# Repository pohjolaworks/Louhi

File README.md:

## Louhi

Louhi is a DIY 50% mechanical keyboard PCB, with an ortho layout. It is meant to be fairly easy to solder and assemble.

Specs:

    Uses a Pro Micro, Elite-C or Proton-C (or any other controller with same form factor)
    Cherry MX Switches, PCB or plate-mount
    Support for multiple bottom layouts
    Uses one pcb-mount stabilizer
    QMK and Vial Compatible

## Supported layouts
  
## Plate
Gasket-mount universal plate files are located in the FR4-Plate folder. Uses 0.75mm thick gasket material on both sides of the plate.

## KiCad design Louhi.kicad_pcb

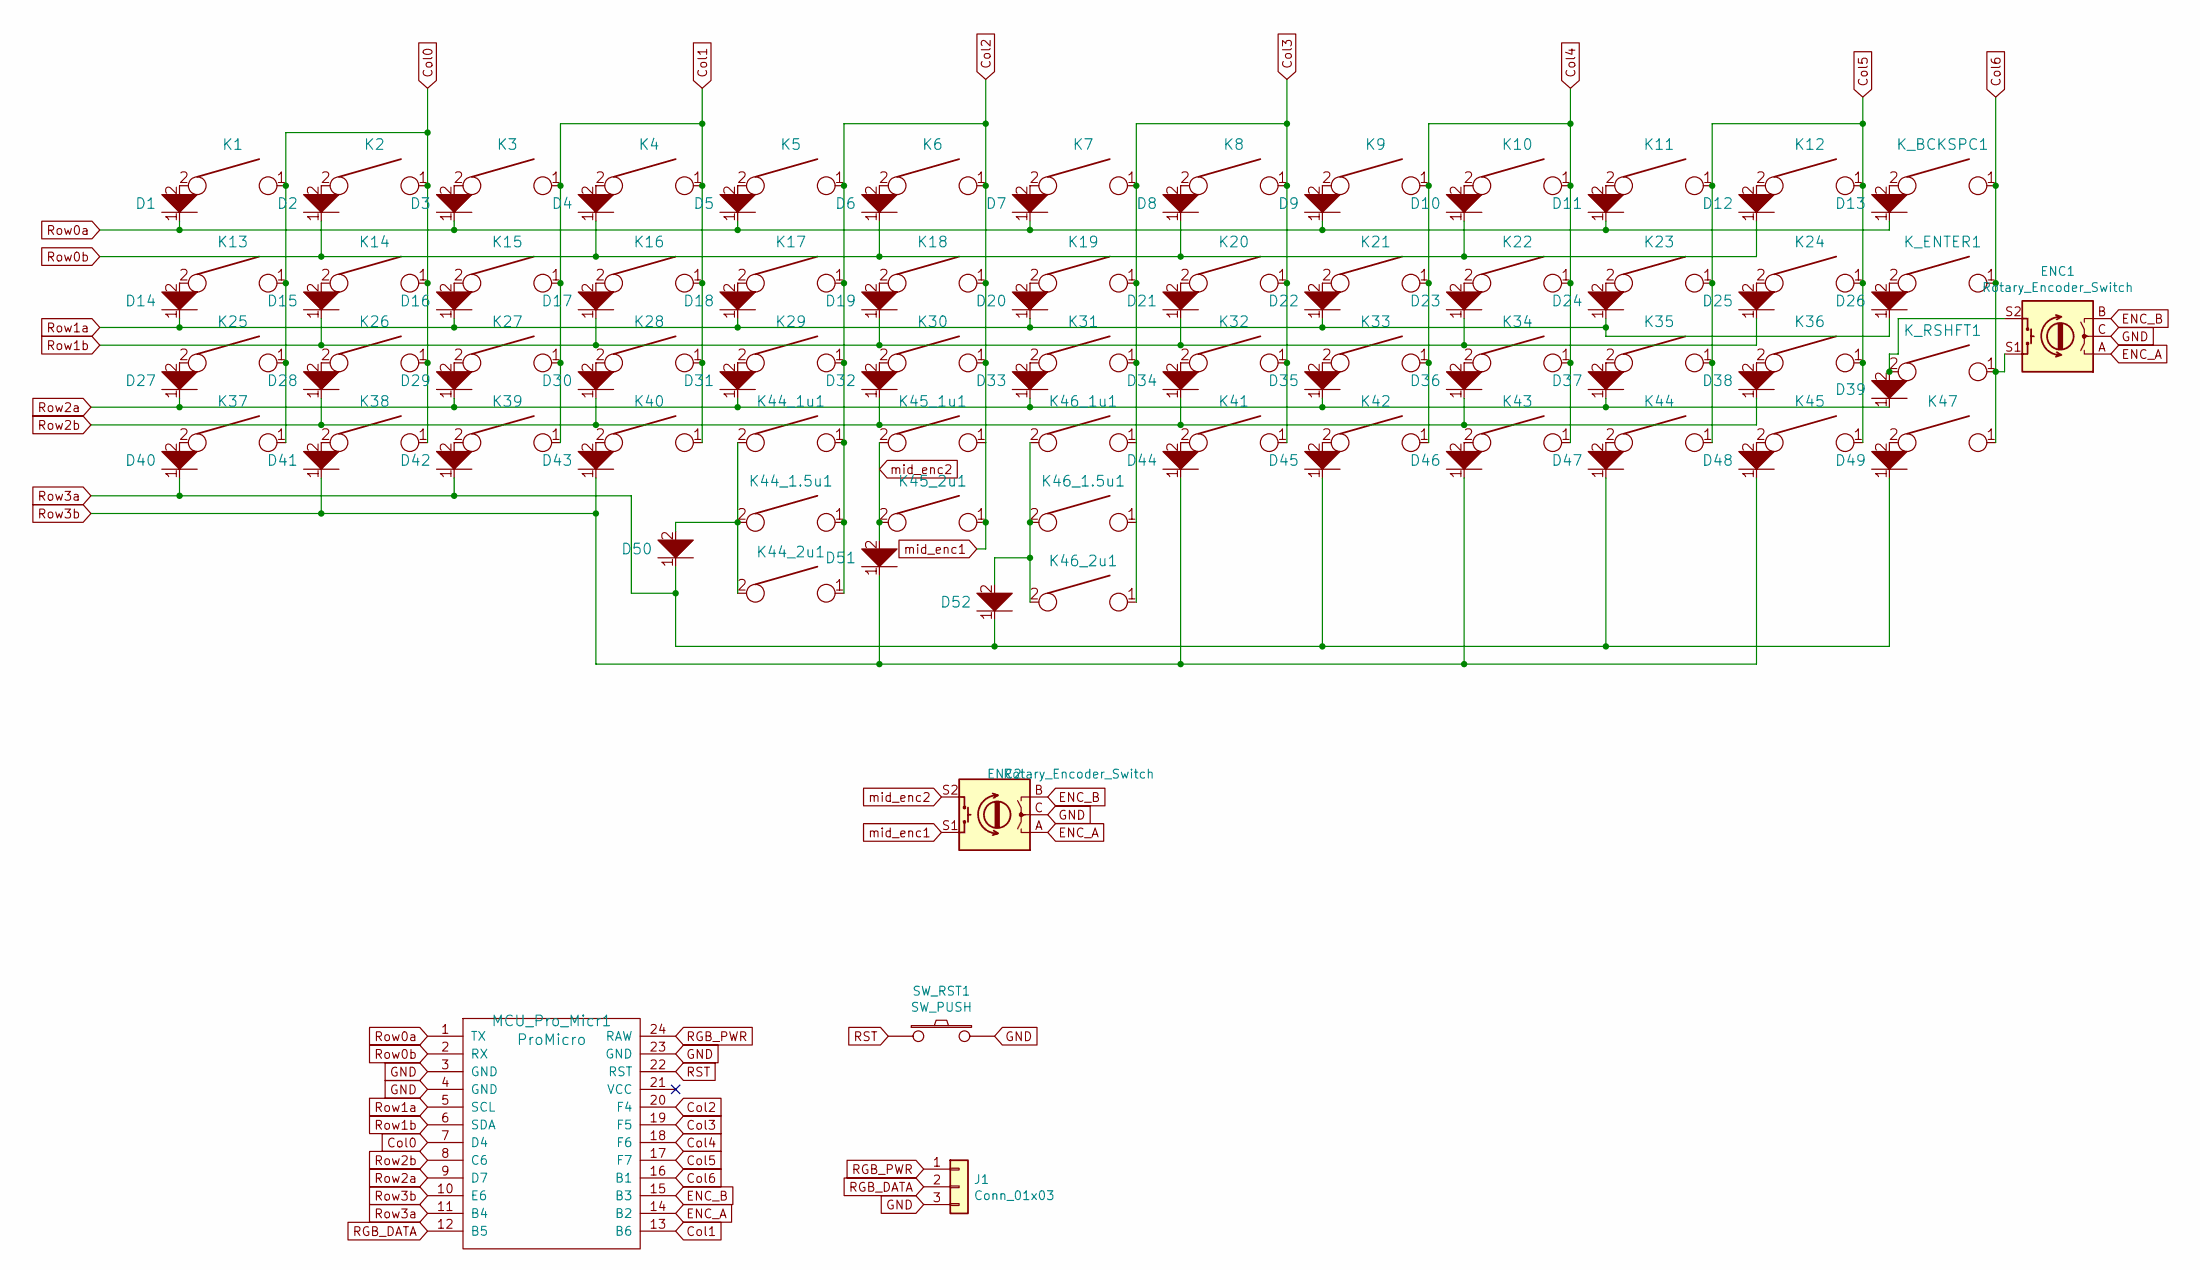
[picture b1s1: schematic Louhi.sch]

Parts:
D1, D2, D3, D4, D5, D6, D7, D8, D9, D10, D11, D12, D13, D14, D15, D16, D17, D18, D19, D20, D21, D22, D23, D24, D25, D26, D27, D28, D29, D30, D31, D32, D33, D34, D35, D36, D37, D38, D39, D40, D41, D42, D43, D44, D45, D46, D47, D48, D49, D50, D51, D52: D; D_SOD123_axial
ENC1, ENC2: Rotary_Encoder_Switch; RotaryEncoder_EC11-no-legs
J1: Conn_01x03; 3_Pin_Jumper
K1, K2, K3, K4, K5, K6, K7, K8, K9, K10, K11, K12, K13, K14, K15, K16, K17, K18, K19, K20, K21, K22, K23, K24, K25, K26, K27, K28, K29, K30, K31, K32, K33, K34, K35, K36, K37, K38, K39, K40, K41, K42, K43, K44, K44_1u1, K45, K45_1u1, K46_1u1, K47: KEYSW; SW_Cherry_MX_1.00u_PCB
K44_1.5u1, K46_1.5u1: KEYSW; SW_Cherry_MX_1.50u_PCB
K44_2u1, K45_2u1, K46_2u1: KEYSW; SW_Cherry_MX_2.00u_PCB
K_BCKSPC1: KEYSW; SW_Cherry_MX_1.00u_PCB
K_ENTER1: KEYSW; SW_Cherry_MX_1.00u_PCB
K_RSHFT1: KEYSW; SW_Cherry_MX_1.00u_PCB
MCU_Pro_Micr1: ProMicro; ArduinoProMicro-BackSide
SW_RST1: SW_PUSH; SW_SPST_TL3342

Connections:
Col0: K1.1, K2.1, K13.1, K14.1, K25.1, K26.1, K37.1, K38.1, MCU_Pro_Micr1.7 (D4)
Col1: K3.1, K4.1, K15.1, K16.1, K27.1, K28.1, K39.1, K40.1, MCU_Pro_Micr1.13 (B6)
Col2: ENC2.S1, K5.1, K6.1, K17.1, K18.1, K29.1, K30.1, K44_1.5u1.1, K44_1u1.1, K44_2u1.1, K45_1u1.1, K45_2u1.1, MCU_Pro_Micr1.20 (F4)
Col3: K7.1, K8.1, K19.1, K20.1, K31.1, K32.1, K41.1, K46_1.5u1.1, K46_1u1.1, K46_2u1.1, MCU_Pro_Micr1.19 (F5)
Col4: K9.1, K10.1, K21.1, K22.1, K33.1, K34.1, K42.1, K43.1, MCU_Pro_Micr1.18 (F6)
Col5: K11.1, K12.1, K23.1, K24.1, K35.1, K36.1, K44.1, K45.1, MCU_Pro_Micr1.17 (F7)
Col6: ENC1.S1, K47.1, K_BCKSPC1.1, K_ENTER1.1, K_RSHFT1.1, MCU_Pro_Micr1.16 (B1)
ENC_A: ENC1.A, ENC2.A, MCU_Pro_Micr1.14 (B2)
ENC_B: ENC1.B, ENC2.B, MCU_Pro_Micr1.15 (B3)
GND: ENC1.C, ENC2.C, J1.3, MCU_Pro_Micr1.3 (GND), MCU_Pro_Micr1.4 (GND), MCU_Pro_Micr1.23 (GND), SW_RST1.2
unnamed: D1.2, K1.2
unnamed: D2.2, K2.2
unnamed: D3.2, K3.2
unnamed: D4.2, K4.2
unnamed: D5.2, K5.2
unnamed: D6.2, K6.2
unnamed: D7.2, K7.2
unnamed: D8.2, K8.2
unnamed: D9.2, K9.2
unnamed: D10.2, K10.2
unnamed: D11.2, K11.2
unnamed: D12.2, K12.2
unnamed: D13.2, K_BCKSPC1.2
unnamed: D14.2, K13.2
unnamed: D15.2, K14.2
unnamed: D16.2, K15.2
unnamed: D17.2, K16.2
unnamed: D18.2, K17.2
unnamed: D19.2, K18.2
unnamed: D20.2, K19.2
unnamed: D21.2, K20.2
unnamed: D22.2, K21.2
unnamed: D23.2, K22.2
unnamed: D24.2, K23.2
unnamed: D25.2, K24.2
unnamed: D26.2, K_ENTER1.2
unnamed: D27.2, K25.2
unnamed: D28.2, K26.2
unnamed: D29.2, K27.2
unnamed: D30.2, K28.2
unnamed: D31.2, K29.2
unnamed: D32.2, K30.2
unnamed: D33.2, K31.2
unnamed: D34.2, K32.2
unnamed: D35.2, K33.2
unnamed: D36.2, K34.2
unnamed: D37.2, K35.2
unnamed: D38.2, K36.2
unnamed: D39.2, ENC1.S2, K_RSHFT1.2
unnamed: D40.2, K37.2
unnamed: D41.2, K38.2
unnamed: D42.2, K39.2
unnamed: D43.2, K40.2
unnamed: D44.2, K41.2
unnamed: D45.2, K42.2
unnamed: D46.2, K43.2
unnamed: D47.2, K44.2
unnamed: D48.2, K45.2
unnamed: D49.2, K47.2
unnamed: D50.2, K44_1.5u1.2, K44_1u1.2, K44_2u1.2
unnamed: D52.2, K46_1.5u1.2, K46_1u1.2, K46_2u1.2
RGB_DATA: J1.2, MCU_Pro_Micr1.12 (B5)
RGB_PWR: J1.1, MCU_Pro_Micr1.24 (RAW)
RST: MCU_Pro_Micr1.22 (RST), SW_RST1.1
Row0a: D1.1, D3.1, D5.1, D7.1, D9.1, D11.1, D13.1, MCU_Pro_Micr1.1 (TX)
Row0b: D2.1, D4.1, D6.1, D8.1, D10.1, D12.1, MCU_Pro_Micr1.2 (RX)
Row1a: D14.1, D16.1, D18.1, D20.1, D22.1, D24.1, D26.1, MCU_Pro_Micr1.5 (SCL)
Row1b: D15.1, D17.1, D19.1, D21.1, D23.1, D25.1, MCU_Pro_Micr1.6 (SDA)
Row2a: D27.1, D29.1, D31.1, D33.1, D35.1, D37.1, D39.1, MCU_Pro_Micr1.9 (D7)
Row2b: D28.1, D30.1, D32.1, D34.1, D36.1, D38.1, MCU_Pro_Micr1.8 (C6)
Row3a: D40.1, D42.1, D45.1, D47.1, D49.1, D50.1, D52.1, MCU_Pro_Micr1.11 (B4)
Row3b: D41.1, D43.1, D44.1, D46.1, D48.1, D51.1, MCU_Pro_Micr1.10 (E6)
mid_enc2: D51.2, ENC2.S2, K45_1u1.2, K45_2u1.2

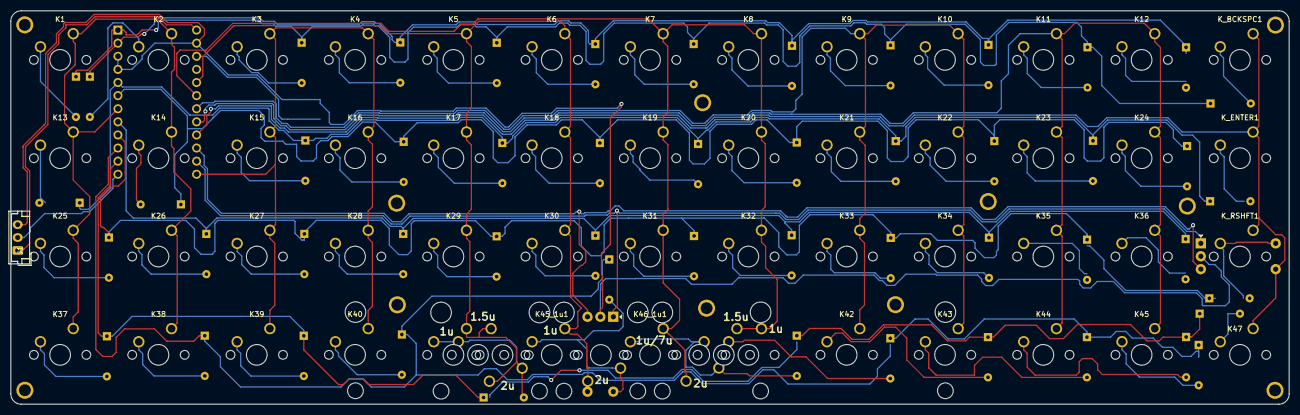
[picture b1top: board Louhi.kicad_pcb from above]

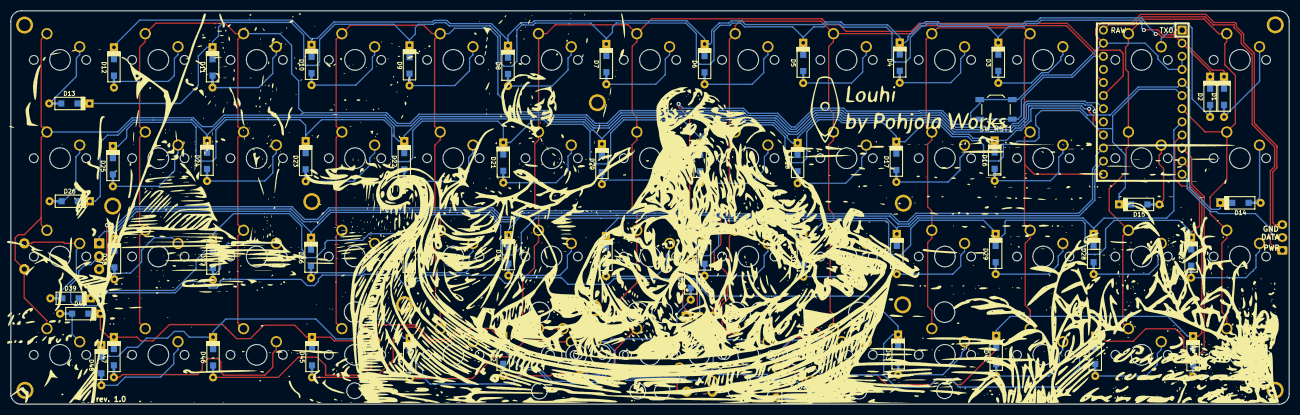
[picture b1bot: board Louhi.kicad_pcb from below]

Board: 2 copper layers, 247.7 x 76.2 mm, 125 parts (53 on the bottom side), 73 nets.

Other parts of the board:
HOLE5, HOLE5#2, HOLE5#3, HOLE5#4, HOLE5#5, HOLE5#6, HOLE5#7, HOLE5#8, HOLE5#9, HOLE5#10, HOLE5#11: MountingHole_4mm; MountingHole_M2

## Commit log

2020-11-30 Initial push
2021-01-08 Add KLE layout file
2021-01-26 Add FR4 gasket plate
2021-07-06 Add images and STEP file
2021-12-14 KLE layout JSON files
2021-12-15 Create LICENSE
2022-02-14 Upload layout KLEs, edit Readme to show layouts
2022-03-09 First versions of stacked acrylic cases
